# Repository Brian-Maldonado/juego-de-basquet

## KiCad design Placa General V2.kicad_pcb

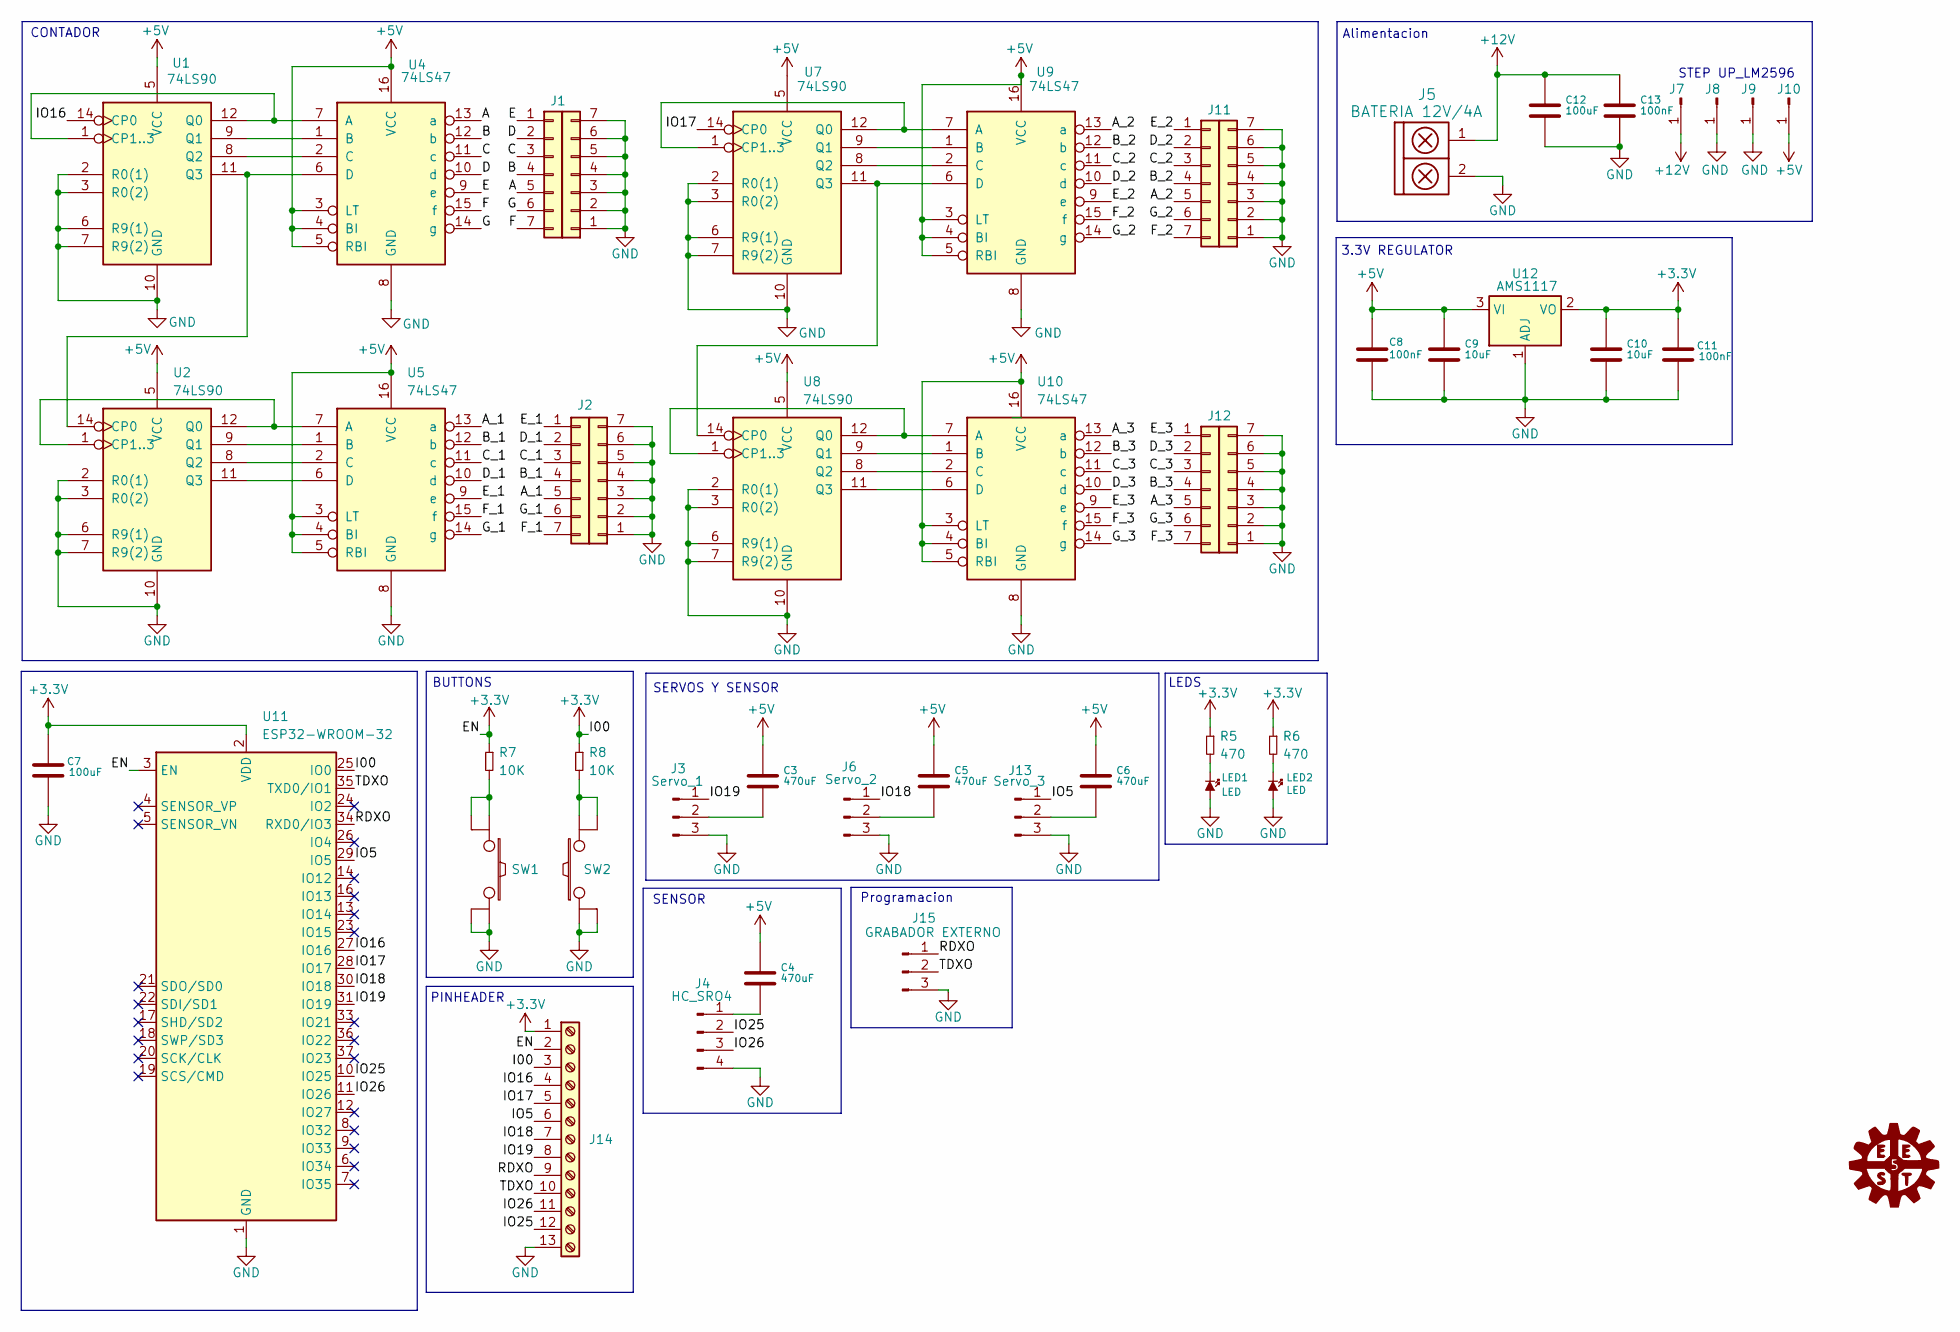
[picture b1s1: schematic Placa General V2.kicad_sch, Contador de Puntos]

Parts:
C3, C4, C5, C6: 470uF; C_1206
C7: 100uF; C_1206
C8, C11: 100nF; C_1206
C9, C10: 10uF; C_1206
C12: 100uF; C_Elec_6.3x7.7
C13: 100nF; C_Rect_L7.2mm_W2.5mm_P5.00mm_FKS2_FKP2_MKS2_MKP2
J1, J2, J11, J12: Conn_01x07; Conector 7X7
J3: Servo_1; PinSocket_1x03_P2.54mm_Vertical
J4: HC_SRO4; PinHeader_1x04_P2.54mm_Vertical
J5: BATERIA 12V/4A; BORNERA2_AZUL
J6: Servo_2; PinSocket_1x03_P2.54mm_Vertical
J7, J8, J9, J10: Conn_01x01_Pin; PinSocket_1x01_P2.54mm_Vertical
J13: Servo_3; PinHeader_1x03_P2.54mm_Vertical
J14: Screw_Terminal_01x13; PinSocket_1x13_P2.54mm_Vertical
J15: GRABADOR EXTERNO; PinSocket_1x03_P2.54mm_Vertical
LED1, LED2: LED; Led_0805
R5, R6: 470; R_1206
R7, R8: 10K; R_1206
SW1: SW_PUSH 1; Pulsador_4_SMD
SW2: SW_PUSH 2; Pulsador_4_SMD
U1, U2, U7, U8: 74LS90; DIP-14_W7.62mm
U4, U5, U9, U10: 74LS47; DIP-16_W7.62mm
U11: ESP32-WROOM-32
U12: AMS1117; SOT-223-3_TabPin2

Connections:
+3.3V: C7.1, C10.1, C11.1, J14.1, J14.2, J14.3, R5.1, R6.1, R7.1, R8.1, U11.2 (VDD), U11.3 (EN), U11.25 (IO0), U12.2 (VO)
+5V: C3.1, C4.1, C5.1, C6.1, C8.1, C9.1, J10.1, U1.5 (VCC), U2.5 (VCC), U4.3 (LT), U4.4 (BI), U4.5 (RBI), U4.16 (VCC), U5.3 (LT), U5.4 (BI), U5.5 (RBI), U5.16 (VCC), U7.5 (VCC), U8.5 (VCC), U9.3 (LT), U9.4 (BI), U9.5 (RBI), U9.16 (VCC), U10.3 (LT), U10.4 (BI), U10.5 (RBI), U10.16 (VCC), U12.3 (VI)
+12V: C12.1, C13.1, J5.1, J7.1
/IO5: J13.1, J14.6, U11.29 (IO5)
/IO16: J14.4, U1.14 (CP0), U11.27 (IO16)
/IO17: J14.5, U7.14 (CP0), U11.28 (IO17)
/IO18: J6.1, J14.7, U11.30 (IO18)
/IO19: J3.1, J14.8, U11.31 (IO19)
/IO25: J4.2, J14.12, U11.10 (IO25)
/IO26: J4.3, J14.11, U11.11 (IO26)
/RDXO: J14.9, J15.1, U11.34 (RXD0/IO3)
/TDXO: J14.10, J15.2, U11.35 (TXD0/IO1)
unnamed: C3.2, J3.2
unnamed: C4.2, J4.1
unnamed: C5.2, J6.2
unnamed: C6.2, J13.2
unnamed: LED1.2 (K), R5.2
unnamed: LED2.2 (K), R6.2
unnamed: R7.2, SW1.1, SW1.2
unnamed: R8.2, SW2.3, SW2.4
unnamed: U1.1 (CP1..3), U1.12 (Q0), U4.7 (A)
unnamed: U1.9 (Q1), U4.1 (B)
unnamed: U1.8 (Q2), U4.2 (C)
unnamed: U1.11 (Q3), U2.14 (CP0), U4.6 (D)
unnamed: U2.1 (CP1..3), U2.12 (Q0), U5.7 (A)
unnamed: U2.9 (Q1), U5.1 (B)
unnamed: U2.8 (Q2), U5.2 (C)
unnamed: U2.11 (Q3), U5.6 (D)
unnamed: U7.1 (CP1..3), U7.12 (Q0), U9.7 (A)
unnamed: U7.9 (Q1), U9.1 (B)
unnamed: U7.8 (Q2), U9.2 (C)
unnamed: U7.11 (Q3), U8.14 (CP0), U9.6 (D)
unnamed: U8.1 (CP1..3), U8.12 (Q0), U10.7 (A)
unnamed: U8.9 (Q1), U10.1 (B)
unnamed: U8.8 (Q2), U10.2 (C)
unnamed: U8.11 (Q3), U10.6 (D)

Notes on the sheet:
BUTTONS
Programacion
PINHEADER
SERVOS Y SENSOR
CONTADOR
3.3V REGULATOR
SENSOR
STEP UP_LM2596
Alimentacion
LEDS

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
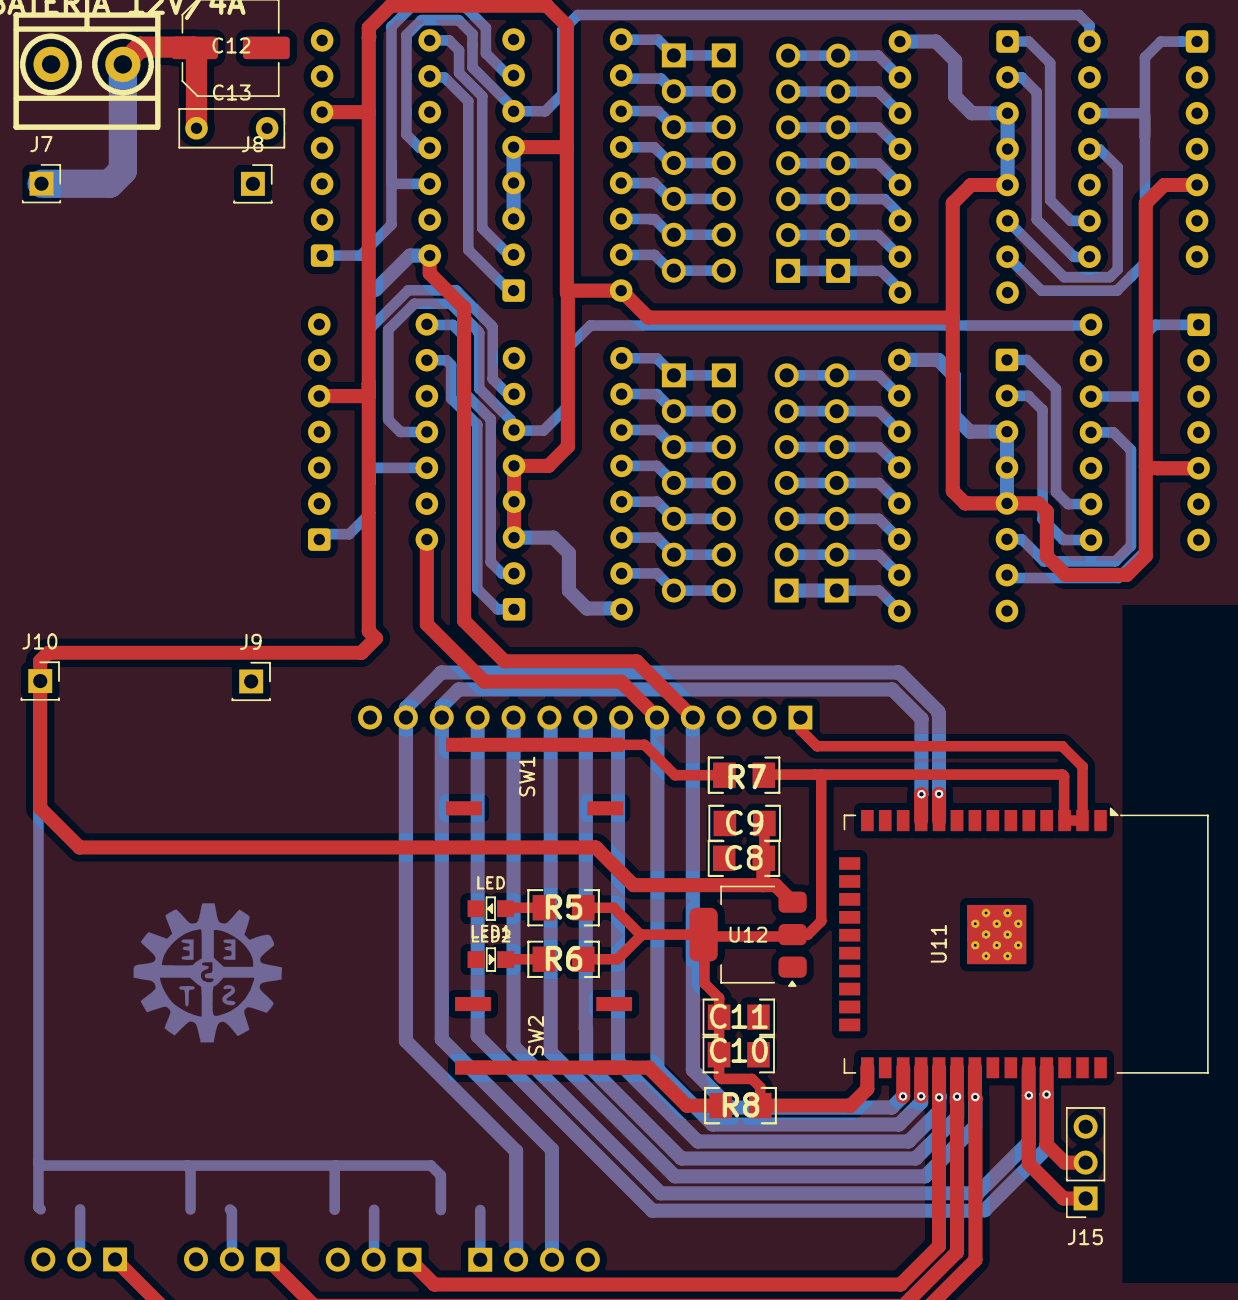
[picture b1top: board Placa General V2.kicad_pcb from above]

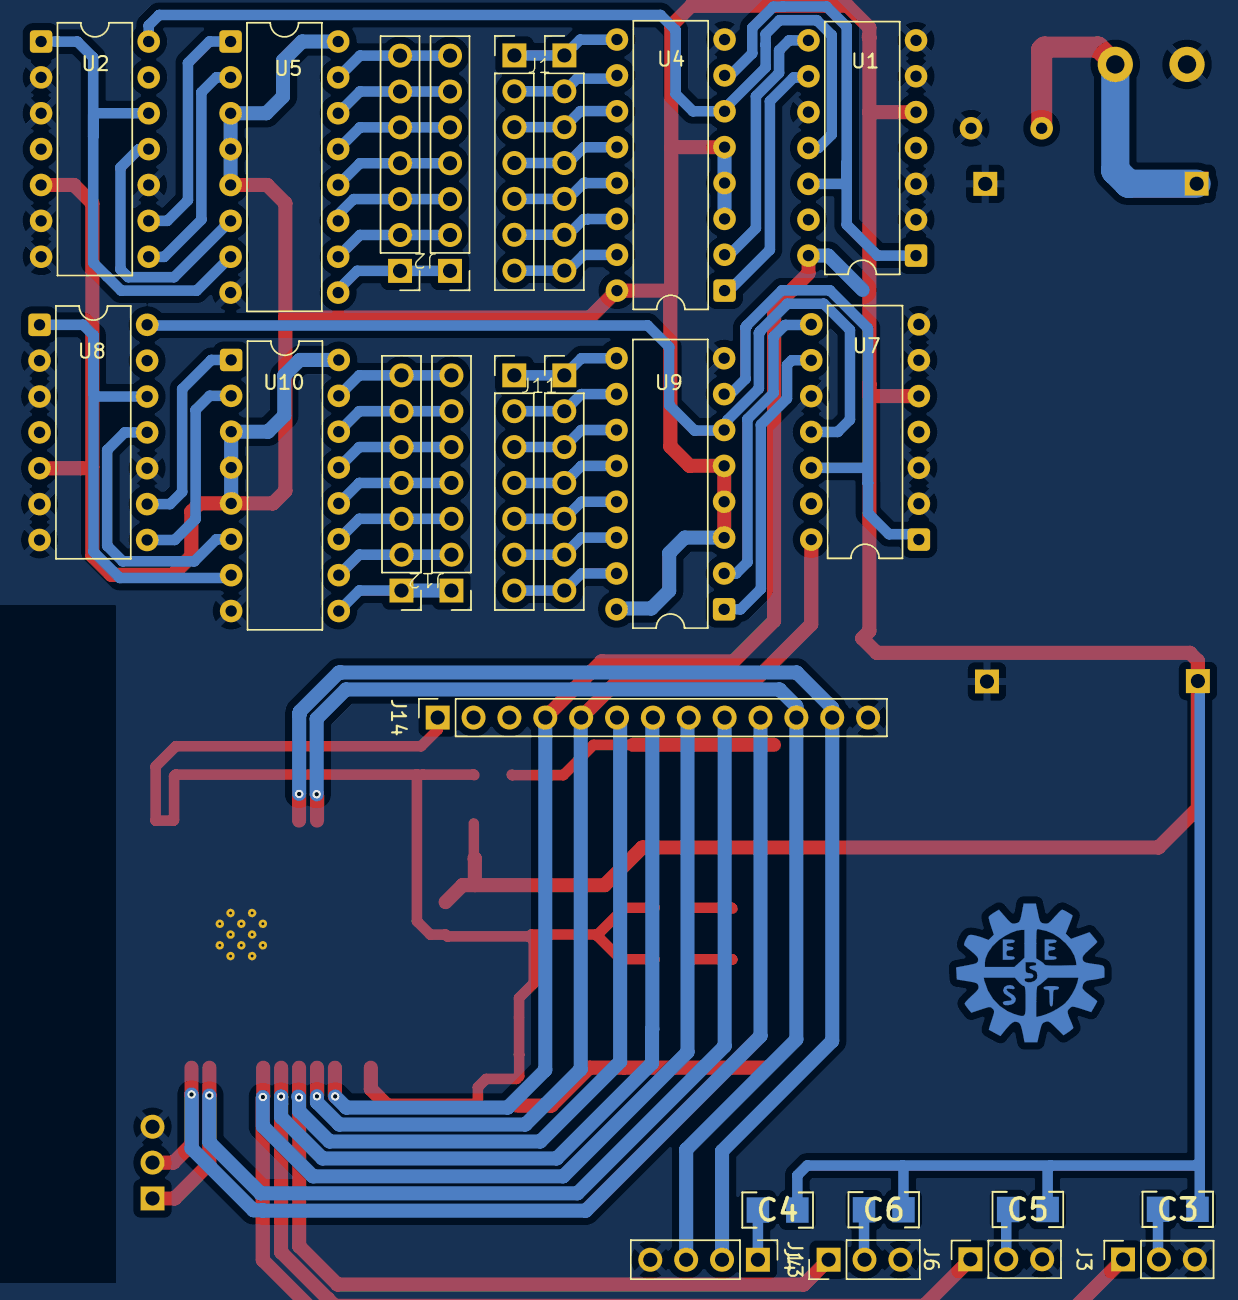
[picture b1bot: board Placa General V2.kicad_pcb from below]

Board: 2 copper layers, 43 parts (21 on the bottom side), 65 nets.

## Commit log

2025-08-14 Hardware
